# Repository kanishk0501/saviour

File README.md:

## Unique Selling Points

1.	Allows you to store all your pertinent medical information such as medications, hospitalization history, allergies, reports, etc. over a single platform.
2.	You can provide with your insurance details so that your insurance company pays for your cause and you don't have to go through the hassle of claims later on.
3.	All this will be connected with a government issued biometric information ID so that all the authenticity of the details is confirmed.
4.	Hospitals can access the patients details through their names.
5. This is an all-in-one system including the deployment of safety measure in case of emergency.

## Implementation
We plan to make a pendant wearable which is going to have electrodes and the ecg sensor to predict heart attacks accurately, moreover, we planned to create a hospital-end of the portal where the emergency services can access the location of the patient from the SOS signal, we also plan to create an app. This app will be accessed by the patient and the ambulance driver for easy communication of the location, so that there is less delay for the emergency services to reach the patients.

## Technology Stack
* 3D-designing
* CAD modelling - Fusion 360
* HTML5 + CSS3
* Javascript
* FireBase
* Arduino
* PCB Designing

## Challenges

* Implementation of Client Side App for generating an SOS to hospital and community in case of a heart attack.
* Hospital Side implementation of the web portal for Information
* Detection of the irregularity in the heartbeat that would signify a heart attack.
* Dealing with False positive in case of detection. 

## Authors

* [Tanay Agrawal](https://github.com/makertanay)
* [Jayendra Dukipatti](https://github.com/Jayendra-Dukkipati)
* [Kanishk Abrol](https://github.com/kanishk0501)
* [Gauri Joshi](https://github.com/kodekandy)

## Steps to view the Web Portal

* Clone the repository to your system or simply dowmload the zip.

* Over Command Line create a local python server with the command: python -m http.server 8000

* View the web portal at : http://localhost:8000/

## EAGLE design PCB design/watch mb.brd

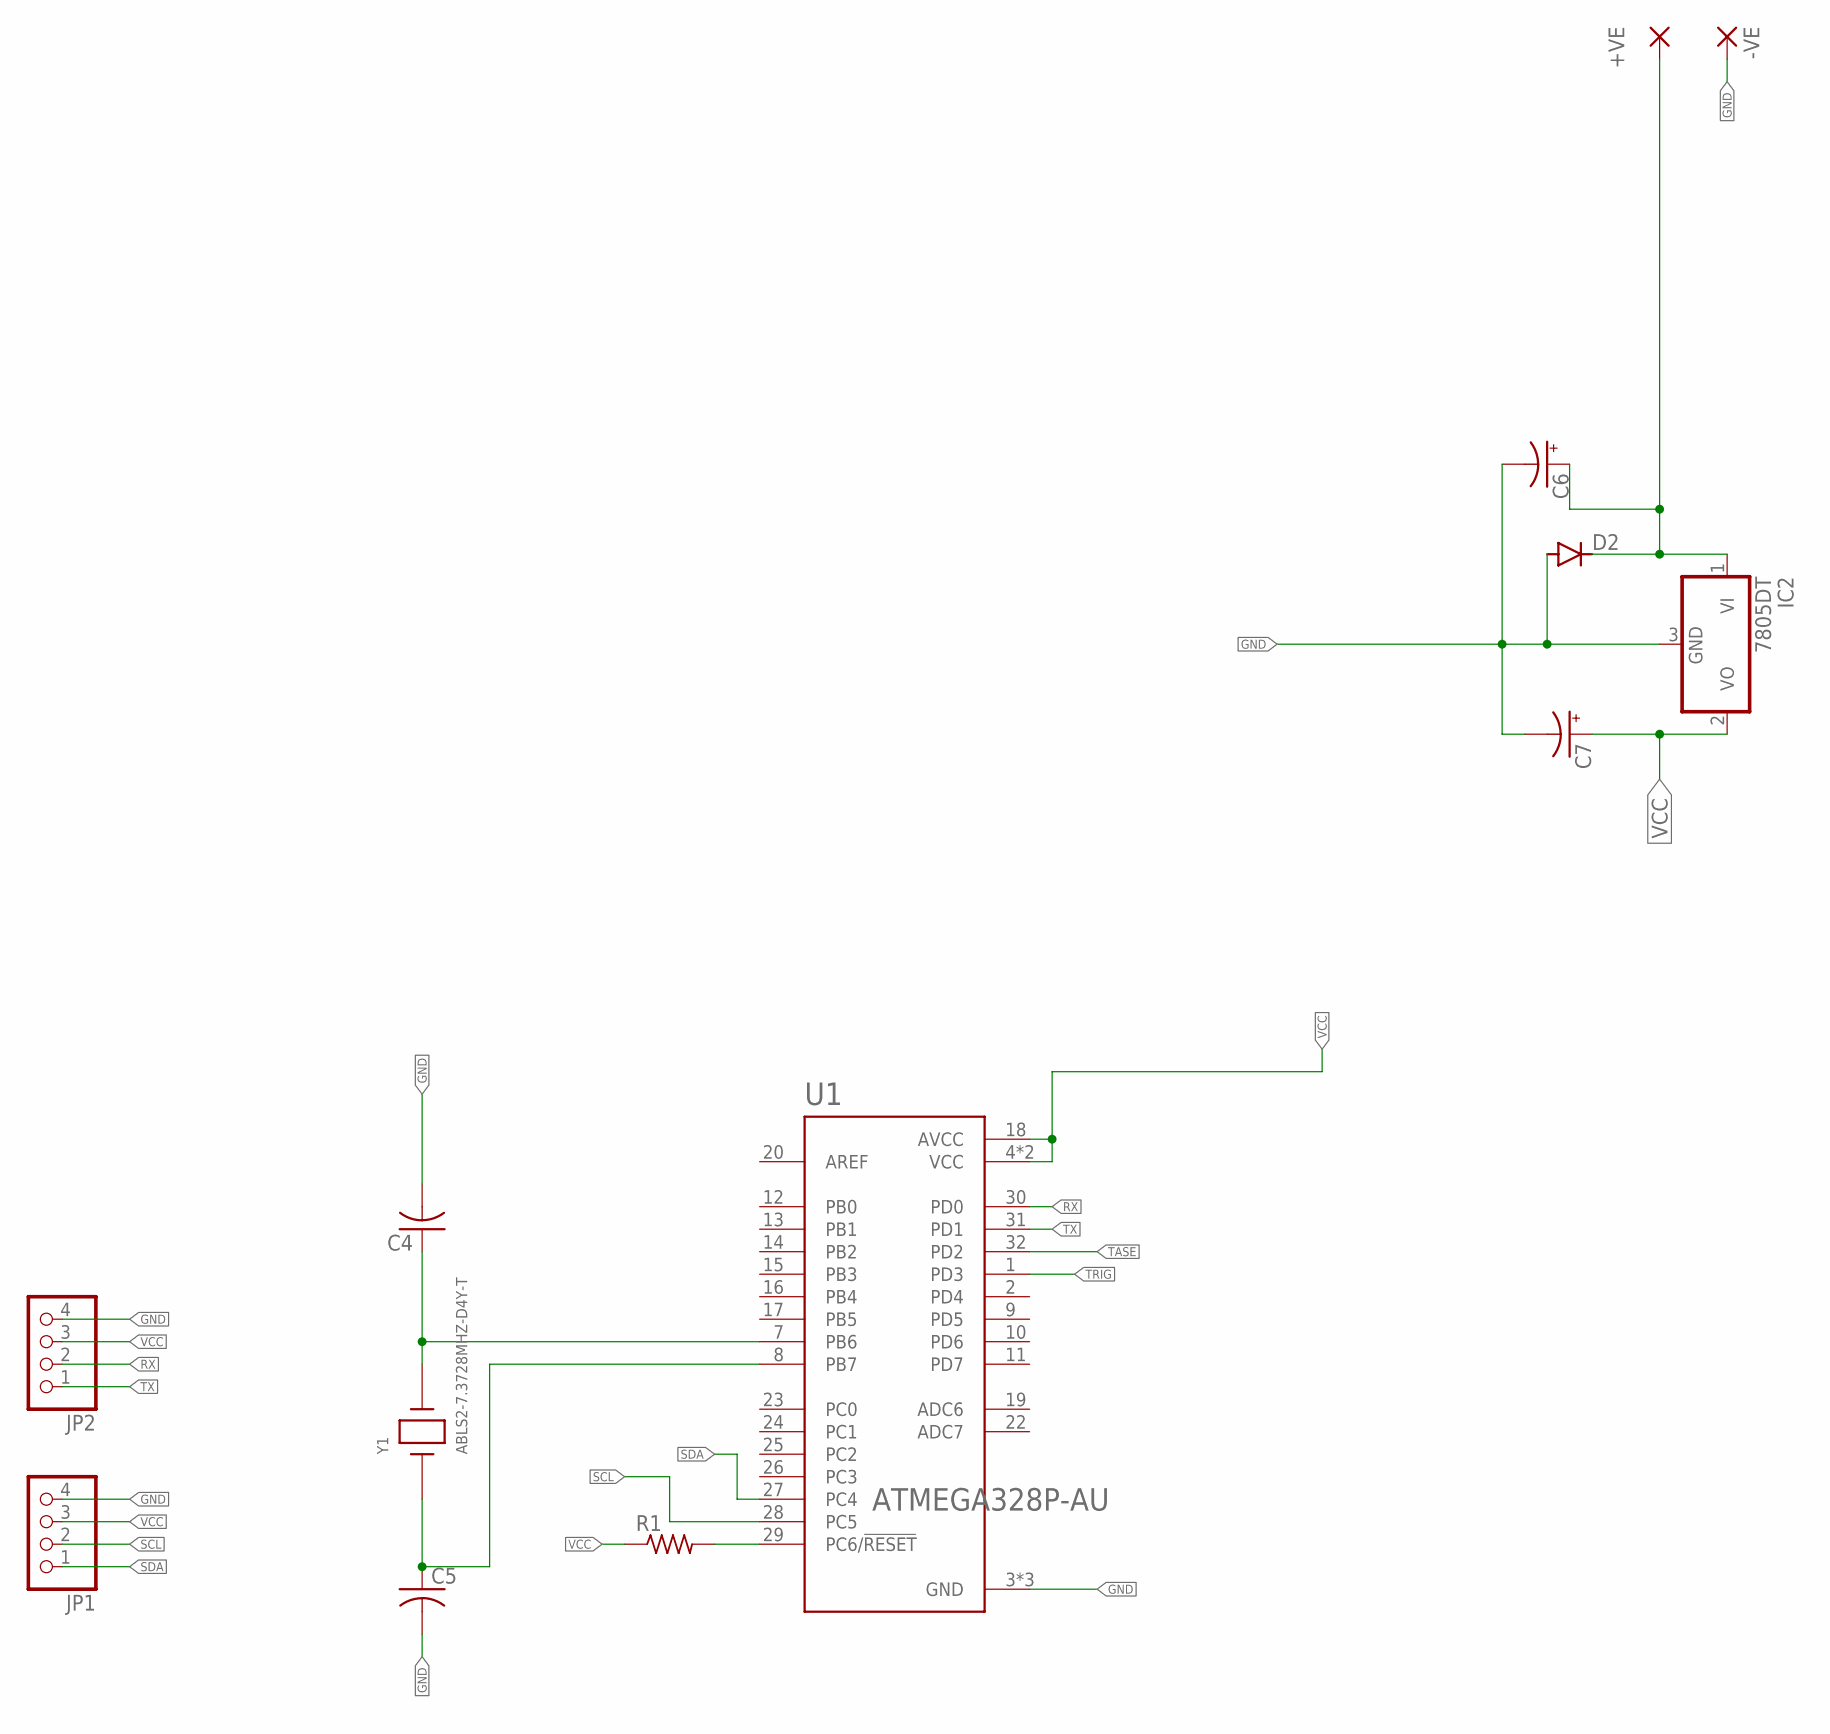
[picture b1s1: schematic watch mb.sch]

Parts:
+VE: WIREPAD1,6/0,8; 1,6/0,8
-VE: WIREPAD1,6/0,8; 1,6/0,8
C4, C5: C-US025-024X044; C025-024X044
C6, C7: CPOL-US153CLV-1010; 153CLV-1010
D2: DIODE-DO214AC; DO214AC
IC2: 7805DT; TO252
JP1, JP2: PINHD-1X4; 1X04
R1: R-US_R0603; R0603
U1: ATMEGA328P-AU; QFP80P900X900X120-32N
Y1: ABLS2-7.3728MHZ-D4Y-T; XTAL_ABLS2-7.3728MHZ-D4Y-T

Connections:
GND: -VE.1, C4.2, C5.2, C6.-, C7.-, D2.A, IC2.3 (GND), JP1.4, JP2.4, U1.3 (GND), U1.5 (GND), U1.21 (GND)
unnamed: +VE.1, C6.+, D2.C, IC2.1 (VI)
unnamed: C4.1, U1.7 (PB6), Y1.2
unnamed: C5.1, U1.8 (PB7), Y1.1
unnamed: R1.2, U1.29 (PC6/!RESET)
RX: JP2.2, U1.30 (PD0)
SCL: JP1.2, U1.28 (PC5)
SDA: JP1.1, U1.27 (PC4)
TASE: U1.32 (PD2)
TRIG: U1.1 (PD3)
TX: JP2.1, U1.31 (PD1)
VCC: C7.+, IC2.2 (VO), JP1.3, JP2.3, R1.1, U1.4 (VCC), U1.6 (VCC), U1.18 (AVCC)

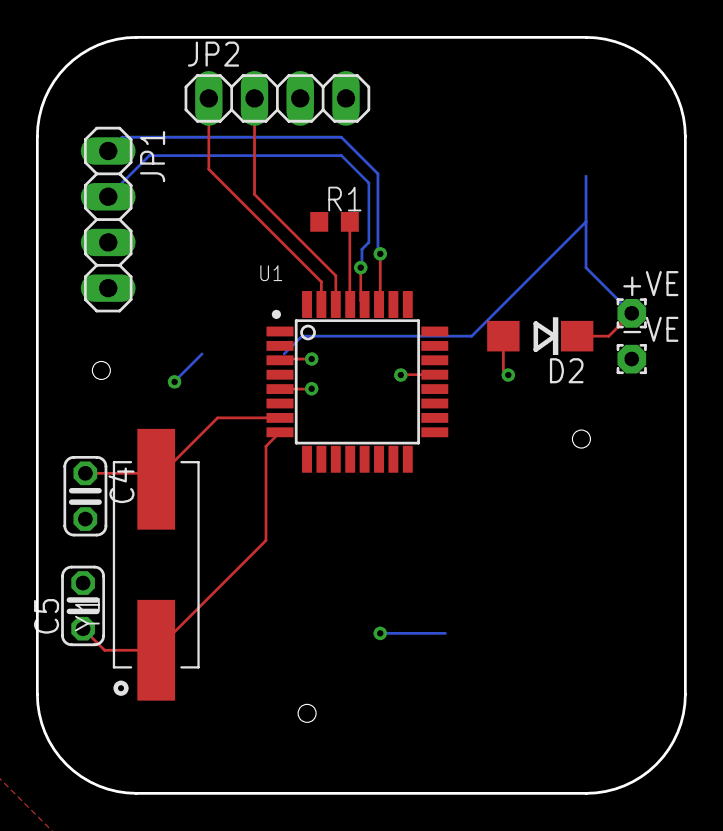
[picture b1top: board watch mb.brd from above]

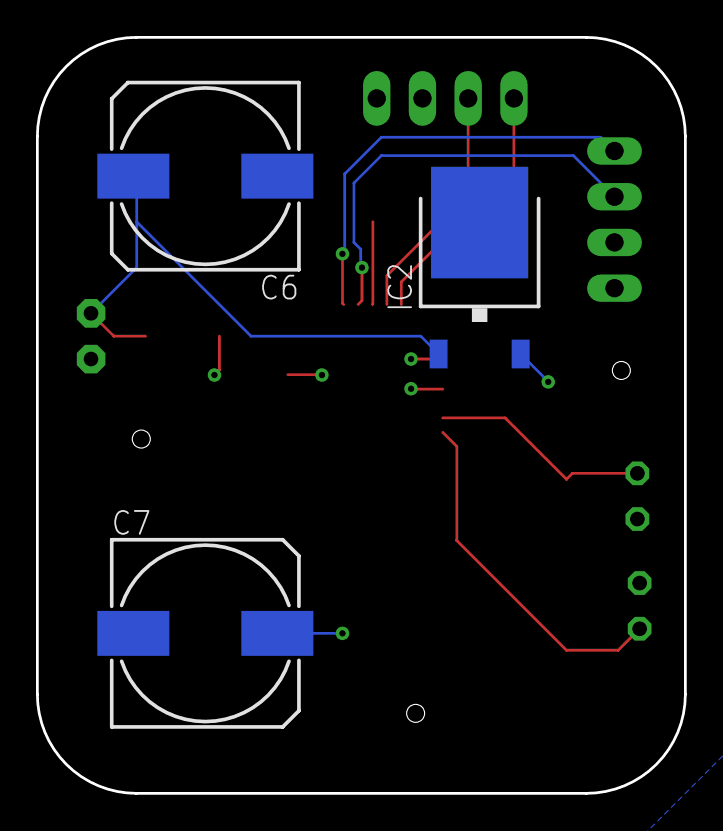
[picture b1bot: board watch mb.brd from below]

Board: 2 copper layers, 36.0 x 42.0 mm, 13 parts (3 on the bottom side), 10 nets.

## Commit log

2021-03-27 First Website Commit :tada:
2021-03-27 progress :hammer:
2021-03-28 patient side webapages
2021-03-28 Folders
2021-03-28 arduino code
2021-03-28 README update
